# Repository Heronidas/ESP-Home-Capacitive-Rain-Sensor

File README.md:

<div align="center">

# 🌧️ ESPHome Capacitive Rain Sensor

**A heated, sealed rain sensor for Home Assistant that tells rain from dew and fog.**<br>
RC-SPC1KA sensor element · ESP32 carrier board · ESPHome firmware

**English** · [Deutsch](README.de.md)

<sub>Rev B carrier board, 100 × 70 mm (KiCad 3D view). The ESP32 D1 mini and the XL6009 module plug in where the outlines are.</sub>

[Features](#-features) · [Status](#-project-status) · [Get started](#-get-started) · [Documentation](#-documentation) · [License](#-license)

</div>

---

## 💡 Why this sensor

Affordable rain sensors use contact grids that corrode within a season, or tipping buckets that report once a measurable amount of water has fallen. Off-the-shelf Zigbee and Wi-Fi rain sensors give you *rain: yes/no* and no way to fix it when they report morning dew as rain.

This sensor works differently:

- **Sealed capacitive element.** The electrodes sit under a sealed surface, so no metal is exposed to corrode. A few drops register.
- **Reads how the level moves.** Rain makes the reading jump; dew and a resting film keep it calm. The firmware starts rain on a fast rise or on jumps; the level alone never starts it.
- **Heated.** After the rain the heater dries the surface in one short run, and it clears frost.
- **Adjustable.** You get the full hardware and firmware. You change thresholds, heater limits and night mode in Home Assistant or on the device's web page, without reflashing.

### Typical uses

- Get notified when it starts to rain, before the laundry on the balcony is wet.
- Close roof windows, skylights, awnings or a pergola roof automatically, and open them again once it is dry.
- Turn on a light when heavy rain darkens the room.
- Pause irrigation during and right after rain.
- Log how long and how often it rained.
- Extend the board with light, pressure, UV or wind sensors and turn it into a small weather station.

---

## ✨ Features

<details open>
<summary><b>Detection</b></summary>

- [x] Weather state: dry or rain, plus a stalled-oscillator state
- [x] Start from the rate of rise on a dry plate and from the jumps on a wet one
- [x] End after a few calm minutes; at night from two calm 5-minute wakes
- [x] Frost lock: no false rain from thawing frost or snow
- [x] Tested in two months outdoors next to a tipping-bucket gauge: rain reported 2–5 minutes before the first tip
- [x] Wetting in % (RC-SPC1KA datasheet curve)

</details>

<details>
<summary><b>Heater control</b></summary>

- [x] One drying run 15 minutes after the rain ends
- [x] Frost heating below 1 °C plate temperature
- [x] Stays off during rain, so the sensor can see it
- [x] Stalled oscillator: one 10-minute drying attempt, then waits
- [x] Adjustable cut-off temperature (default 45 °C, at most 60 °C), checked every second
- [x] Heating-time budget with enforced pause; no new pulse on a low battery
- [x] Safe defaults: off after reset, off on an implausible NTC reading (open or shorted wire)

</details>

<details>
<summary><b>Connectivity and power</b></summary>

- [x] Home Assistant via the native ESPHome API
- [x] Standalone variant: local web page and MQTT (FHEM, ioBroker, Node-RED, Home Assistant MQTT discovery)
- [x] Encrypted OTA updates over Wi-Fi (Home Assistant variant)
- [x] Optional night mode: deep sleep with 5 min wake interval (needs a supply that stays on at low load)
- [x] Battery voltage monitoring
- [x] All settings adjustable at runtime, stored across reboots and sleep
- [x] German and English entity names

</details>

<details>
<summary><b>Hardware</b></summary>

- [x] Carrier board Rev B, 100 × 70 mm, 2 layers; JLCPCB places the SMD parts
- [x] ESP32 D1 mini and XL6009 heater module plug in; flash over the D1 mini's USB port
- [x] Runs from a single 5 V supply; the XL6009 makes the 12 V for the heater
- [x] Heater current on its own return path, away from the oscillator ground
- [x] HTU21D on board for the enclosure climate
- [x] I2C on socket, pin header and screw terminal; 8-pin expansion header
- [x] Supported add-ons: VEML7700 light sensor
- [ ] BME280, LTR390, anemometer, wind vane, tipping bucket (snippets in the wiki, untested)
- [x] 3D-printable sensor holder, also on [MakerWorld](https://makerworld.com/en/models/3655333-heated-rain-sensor-for-home-assistant) with a print profile
- [x] Perfboard build from modules as an alternative

</details>

---

## 🚦 Project status

| Part | Status |
|---|---|
| Firmware, German, Home Assistant API | ✅ Running outdoors on the Rev A board since 24 October |
| Firmware, English and MQTT variants | 🟡 Same logic, generated from the German file; compile in CI, not yet run on a device |
| Rain detection in real rain | ✅ Tested on more than ten rain days next to a tipping-bucket gauge, including two days of steady rain |
| Rev A carrier board | ✅ Runs outdoors with an external XL6009 heater module, R1 = 38.7 kΩ and the series capacitor; no oscillator stall since 7 November |
| Rev B carrier board | ⚪ Layout done with the Rev A fixes (R1 47 kΩ, series capacitor C3), DRC clean, fabrication files in the repo; not yet ordered |
| Sensor holder | ✅ 45° holder outdoors since 24 October |
| Weather add-ons | ⚪ Prepared in the YAML, untested |

How it got here: [Milestones](docs/wiki/Milestones.md) · What comes next: [Roadmap](docs/wiki/Roadmap.md)

---

## 🚀 Get started

1. **Parts.** The board from JLCPCB with an ESP32 D1 mini and an XL6009 module ([ordering](docs/wiki/Ordering-the-Board.md)), or a build from modules on perfboard ([Module Build Guide, PDF](docs/module-build-guide.pdf)), plus an RC-SPC1KA ([parts](docs/wiki/Parts.md)).
2. **Wiring.** Sensor to the SENSOR and HEATER terminals, 5 V to POWER IN ([wiring](docs/wiki/Wiring.md)).
3. **Flashing.** Flash the D1 mini once over USB with a device config that loads the firmware from this repository; later updates go over Wi-Fi ([flashing and updates](docs/wiki/Flashing-and-Updates.md)).
4. **Calibration.** Measure the dry frequency outdoors, check the thresholds ([calibration](docs/wiki/Calibration.md)).
5. **Home Assistant.** Home Assistant discovers the device. Without Home Assistant, use the [MQTT and web page](docs/wiki/MQTT-and-Web-Page.md) variant.

---

## 📚 Documentation

The **[wiki](docs/wiki/Home.md)** has the details:

| | |
|---|---|
| Getting started | [Parts](docs/wiki/Parts.md) · [Wiring](docs/wiki/Wiring.md) · [Flashing and updates](docs/wiki/Flashing-and-Updates.md) · [Calibration](docs/wiki/Calibration.md) |
| Build | [Ordering the board](docs/wiki/Ordering-the-Board.md) · [Module build](docs/wiki/Module-Build.md) · [Sensor holder](docs/wiki/Sensor-Holder.md) · [Board dimensions](docs/wiki/Board-Reference.md#dimensions) |
| Home Assistant | [Entities](docs/wiki/Entities.md) · [MQTT and web page](docs/wiki/MQTT-and-Web-Page.md) |
| How it works | [Measurement, rain or not, heater](docs/wiki/How-It-Works.md) |
| Reference | [Board reference](docs/wiki/Board-Reference.md) · [Extensions](docs/wiki/Extensions.md) · [Troubleshooting](docs/wiki/Troubleshooting.md) · [Known limitations](docs/wiki/Known-Limitations.md) |
| Project | [Milestones](docs/wiki/Milestones.md) · [Roadmap](docs/wiki/Roadmap.md) |

---

## 📁 Repository layout

| Path | Content |
|---|---|
| `firmware/` | ESPHome firmware: `regensensor_de/_en.yaml` (Home Assistant API), `regensensor_mqtt_de/_en.yaml` (web page and MQTT); `examples/` device configs that load it from GitHub |
| `hardware/` | KiCad project of the Rev B board (schematic, PCB, own symbols and footprints for D1 mini and XL6009) |
| `fabrication/` | Gerbers, drill files, JLCPCB BOM and CPL |
| `3d-files/` | Sensor holder STLs for 3D printing, board outline DXF for CAD |
| `docs/` | Wiki pages (`docs/wiki/`), images, Module Build Guide (PDF) and its source (`docs/build-guide/`) |
| `tools/` | Python scripts (KiCad 8 `pcbnew`, Freerouting) generating schematic, PCB, fabrication files and the dimension drawing from `design.py`; `regen_replay.py` replays a device log through the rain detection; `wiki_sync.py` mirrors `docs/wiki/` into the GitHub wiki |
| `.github/workflows/` | CI: firmware check of all four variants (`firmware.yml`), wiki mirror (`wiki.yml`), DRC and Gerber export (`fab.yml`) |

---

## ☕ Support

If this project saved you time, you can support it on Ko-fi.

---

## 📄 License

The firmware is open source under the GPL. You may use the hardware for private and non-commercial purposes; commercial use needs my written permission, and I offer commercial licenses on request.

| Part | License |
|---|---|
| Hardware, fabrication files, sensor holder, documentation | [CC BY-NC-SA 4.0](LICENSES/CC-BY-NC-SA-4.0.txt) |
| Firmware and tools | [GPL-3.0-or-later](LICENSES/GPL-3.0.txt) |

If you build on this project, I'd appreciate a mention with a link back to this repository. The license does not require it.

[`LICENSE.md`](LICENSE.md) has the details, including passing on spare boards at cost.

<sub>RC-SPC1KA is a product of Radiocontrolli S.r.l. This project is independent and not affiliated with or endorsed by Radiocontrolli.</sub>

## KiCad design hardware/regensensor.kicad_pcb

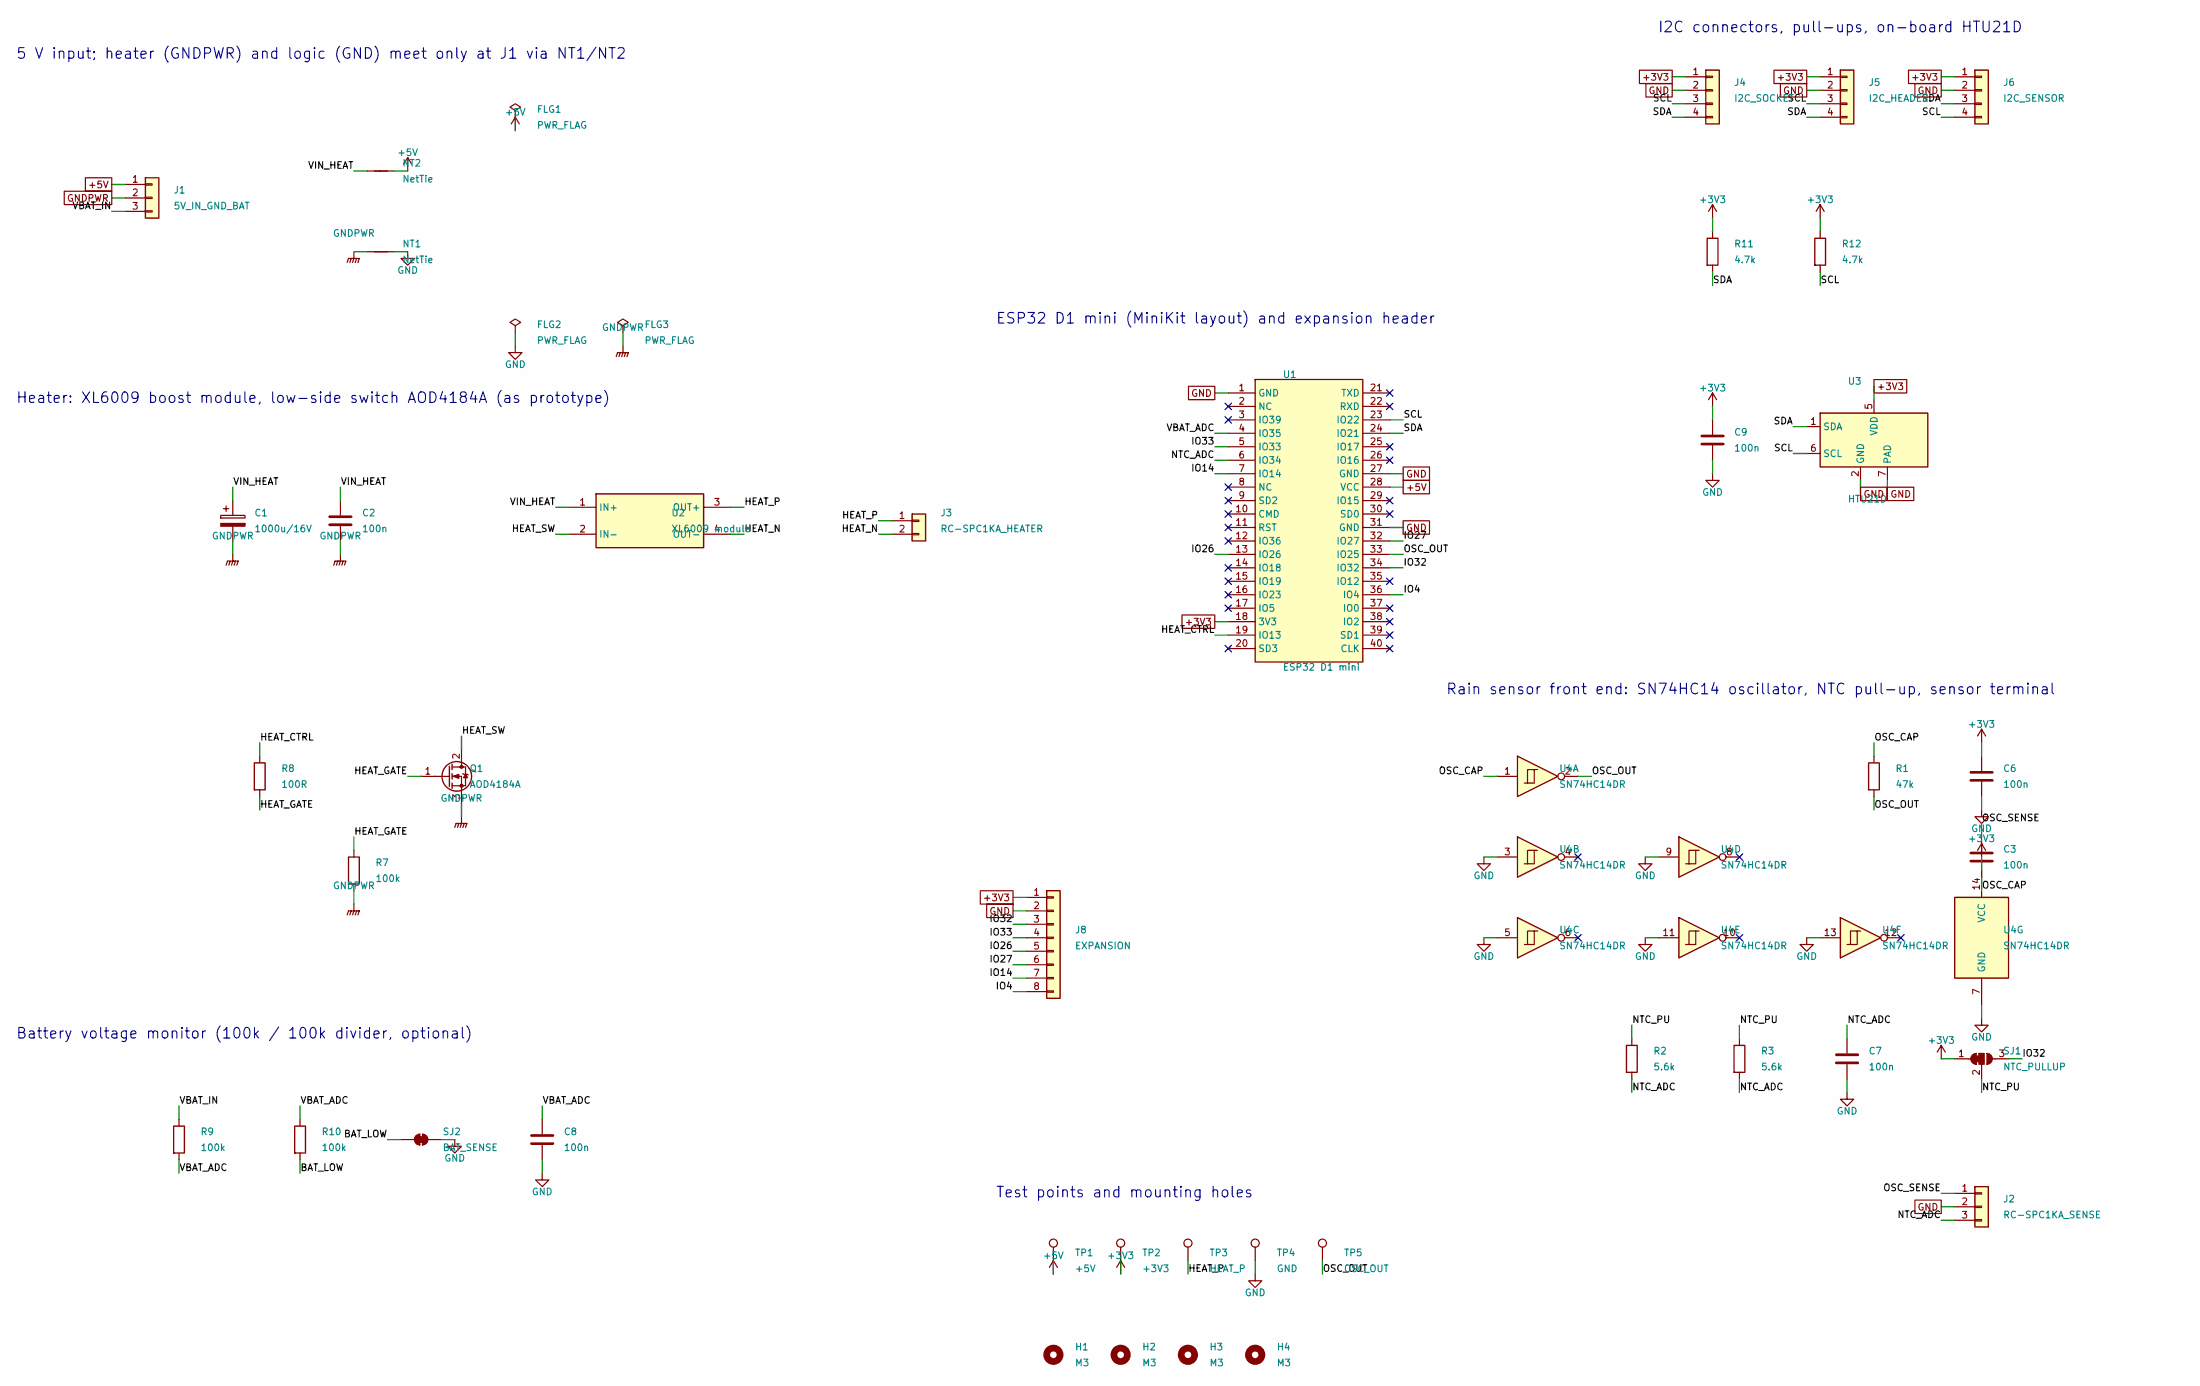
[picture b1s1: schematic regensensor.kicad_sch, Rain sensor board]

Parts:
C1: 1000u/16V; CP_Radial_D10.0mm_P5.00mm
C2, C3, C6, C7, C8, C9: 100n; C_0805_2012Metric; LCSC C49678
FLG1, FLG2, FLG3: PWR_FLAG
H1, H2, H3, H4: M3; MountingHole_3.2mm_M3
J1: 5V_IN_GND_BAT; TerminalBlock_Phoenix_MKDS-1,5-3-5.08_1x03_P5.08mm_Horizont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
J2: RC-SPC1KA_SENSE; TerminalBlock_Phoenix_MKDS-1,5-3-5.08_1x03_P5.08mm_Horizont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
J3: RC-SPC1KA_HEATER; TerminalBlock_Phoenix_MKDS-1,5-2-5.08_1x02_P5.08mm_Horizont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
J4: I2C_SOCKET; PinSocket_1x04_P2.54mm_Vertical
J5: I2C_HEADER; PinHeader_1x04_P2.54mm_Vertical
J6: I2C_SENSOR; TerminalBlock_Phoenix_MKDS-1,5-4-5.08_1x04_P5.08mm_Horizont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
J8: EXPANSION; PinHeader_1x08_P2.54mm_Vertical
NT1: NetTie; NetTie-2_SMD_Pad0.5mm
NT2: NetTie; NetTie-2_SMD_Pad2.0mm
Q1: AOD4184A; TO-252-2; LCSC C99124
R1: 47k; R_0805_2012Metric; LCSC C17713
R2, R3: 5.6k; R_0805_2012Metric; LCSC C4382
R7, R9, R10: 100k; R_0603_1608Metric; LCSC C25803
R8: 100R; R_0805_2012Metric; LCSC C17408
R11, R12: 4.7k; R_0805_2012Metric; LCSC C17673
SJ1: NTC_PULLUP; SolderJumper-3_P1.3mm_Bridged12_RoundedPad1.0x1.5mm
SJ2: BAT_SENSE; SolderJumper-2_P1.3mm_Bridged_RoundedPad1.0x1.5mm
TP1: +5V; TestPoint_Pad_D1.5mm
TP2: +3V3; TestPoint_Pad_D1.5mm
TP3: HEAT_P; TestPoint_Pad_D1.5mm
TP4: GND; TestPoint_Pad_D1.5mm
TP5: OSC_OUT; TestPoint_Pad_D1.5mm
U1: ESP32 D1 mini; ESP32_MiniKit
U2: XL6009 module; XL6009_Module
U3: HTU21D; DFN-6-1EP_3x3mm_P1mm_EP1.5x2.4mm; LCSC C83479
U4: SN74HC14DR; SOIC-14_3.9x8.7mm_P1.27mm; LCSC C6820

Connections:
+3V3: C6.1, C9.1, J4.1, J5.1, J6.1, J8.1, R11.1, R12.1, SJ1.1 (A), TP2.1, U1.18 (3V3), U3.5 (VDD), U4.14 (VCC)
+5V: FLG1.1, J1.1, NT2.2, TP1.1, U1.28 (VCC)
/BAT_LOW: R10.2, SJ2.1 (A)
/HEAT_CTRL: R8.1, U1.19 (IO13)
/HEAT_GATE: Q1.1 (G), R7.1, R8.2
/HEAT_N: J3.2, U2.4 (OUT-)
/HEAT_P: J3.1, TP3.1, U2.3 (OUT+)
/HEAT_SW: Q1.2 (D), U2.2 (IN-)
/IO4: J8.8, U1.36 (IO4)
/IO14: J8.7, U1.7 (IO14)
/IO26: J8.5, U1.13 (IO26)
/IO27: J8.6, U1.32 (IO27)
/IO32: J8.3, SJ1.3 (B), U1.34 (IO32)
/IO33: J8.4, U1.5 (IO33)
/NTC_ADC: C7.1, J2.3, R2.2, R3.2, U1.6 (IO34)
/NTC_PU: R2.1, R3.1, SJ1.2 (C)
/OSC_CAP: C3.2, R1.1, U4.1
/OSC_OUT: R1.2, TP5.1, U1.33 (IO25), U4.2
/OSC_SENSE: C3.1, J2.1
/SCL: J4.3, J5.3, J6.4, R12.2, U1.23 (IO22), U3.6 (SCL)
/SDA: J4.4, J5.4, J6.3, R11.2, U1.24 (IO21), U3.1 (SDA)
/VBAT_ADC: C8.1, R9.2, R10.1, U1.4 (IO35)
/VBAT_IN: J1.3, R9.1
/VIN_HEAT: C1.1, C2.1, NT2.1, U2.1 (IN+)
GND: C6.2, C7.2, C8.2, C9.2, FLG2.1, J2.2, J4.2, J5.2, J6.2, J8.2, NT1.2, SJ2.2 (B), TP4.1, U1.1 (GND), U1.27 (GND), U1.31 (GND), U3.2 (GND), U3.7 (PAD), U4.3, U4.5, U4.7 (GND), U4.9, U4.11, U4.13
GNDPWR: C1.2, C2.2, FLG3.1, J1.2, NT1.1, Q1.3 (S), R7.2

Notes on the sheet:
5 V input; heater (GNDPWR) and logic (GND) meet only at J1 via NT1/NT2
Heater: XL6009 boost module, low-side switch AOD4184A (as prototype)
Battery voltage monitor (100k / 100k divider, optional)
ESP32 D1 mini (MiniKit layout) and expansion header
I2C connectors, pull-ups, on-board HTU21D
Rain sensor front end: SN74HC14 oscillator, NTC pull-up, sensor terminal
Test points and mounting holes

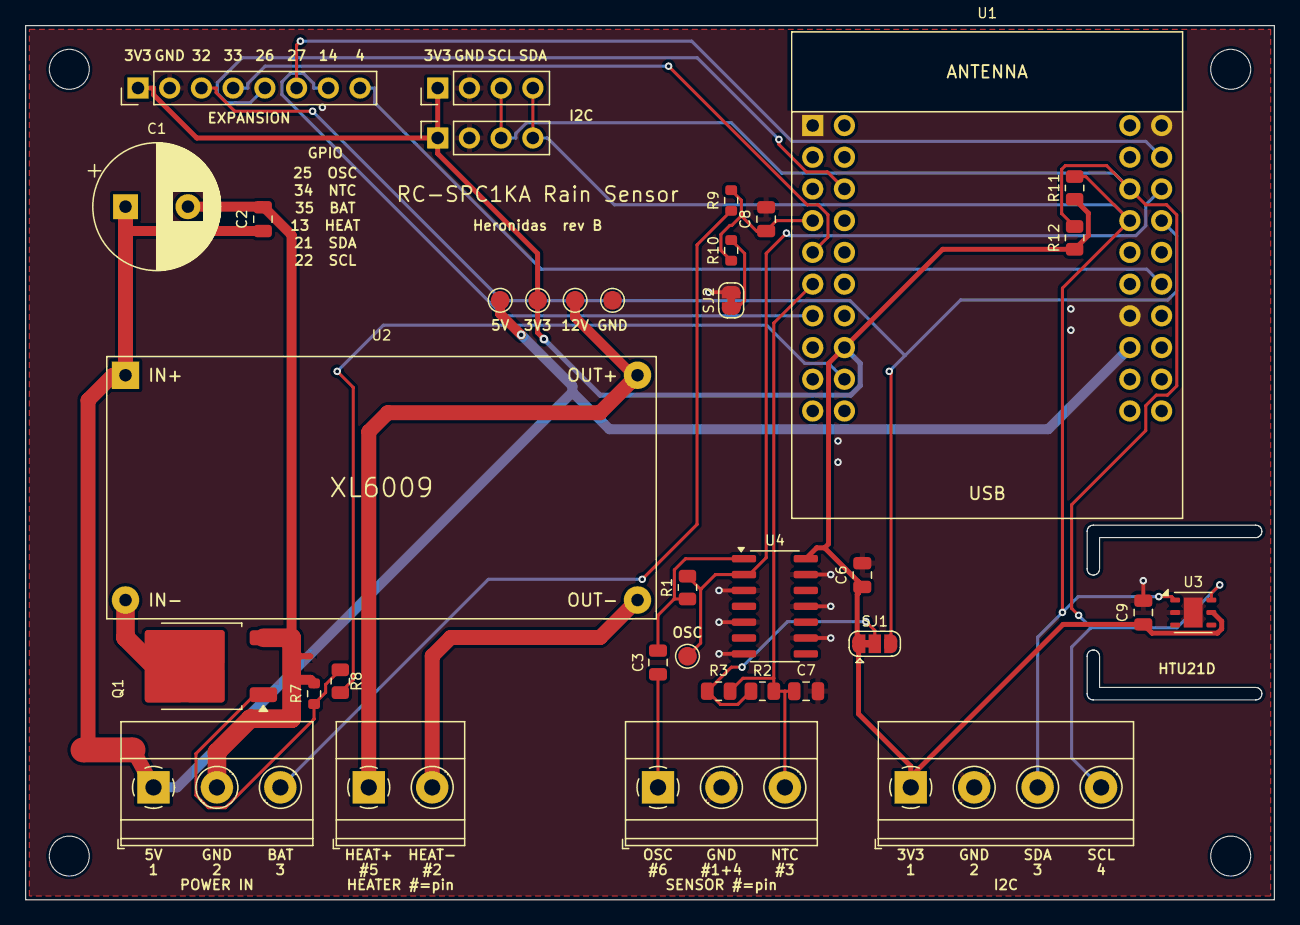
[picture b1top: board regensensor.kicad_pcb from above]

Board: 2 copper layers, 100.0 x 70.0 mm, 41 parts (0 on the bottom side), 26 nets.

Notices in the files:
README.md:
Firmware: GPL-3.0
Hardware: CC BY-NC-SA 4.0
hardware/regensensor.kicad_pcb:
© 2026 · CC BY-NC-SA
